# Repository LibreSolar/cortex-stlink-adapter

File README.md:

# Cortex ST-Link Adapter

This adapter allows to connect the ST-Link V2 (STM32 Nucleo boards) to be connected to the small 10-pin Cortex standard connectors.

The ST-Link can be used as a serial wire debug (SWD) interface.

## Schematic

The jumper JP1 can be used to connect the SWO pin (serial wire output) to the RX pin of the nucleo board, thus allowing serial communications with MCUs which don't have SWO (Cortex M0 like STM32F072 for example). This works only if the Cortex SWO pin is wired to a TX pin of the MCU, of course.

The pull-up resistor is useful to put NRST to a defined state.

The additional capacitor C1 can be used to stabilize the supply voltage, but might not be necessary.

## Original pictures

### Top side

### Bottom side (fits to ST-Link on Nucleo Board)

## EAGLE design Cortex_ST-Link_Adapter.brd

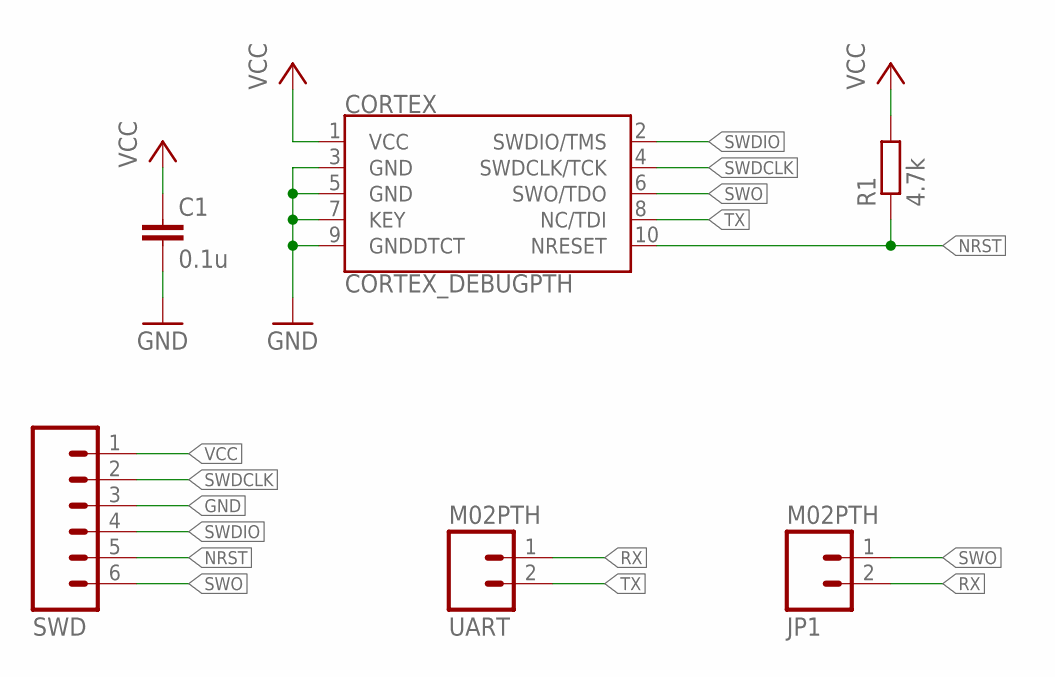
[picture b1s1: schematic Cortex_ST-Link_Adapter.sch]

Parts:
C1: 0.1u; C0805
CORTEX: CORTEX_DEBUGPTH; 2X5-PTH-1.27MM
JP1: M02PTH; 1X02
R1: 4.7k; R0805
SWD: M06SILK_FEMALE_PTH; 1X06
UART: M02PTH; 1X02

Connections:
GND: C1.2, CORTEX.3 (GND), CORTEX.5 (GND), CORTEX.7 (KEY), CORTEX.9 (GNDDTCT), SWD.3
NRST: CORTEX.10 (NRESET), R1.1, SWD.5
RX: JP1.2, UART.1
SWDCLK: CORTEX.4 (SWDCLK/TCK), SWD.2
SWDIO: CORTEX.2 (SWDIO/TMS), SWD.4
SWO: CORTEX.6 (SWO/TDO), JP1.1, SWD.6
TX: CORTEX.8 (NC/TDI), UART.2
VCC: C1.1, CORTEX.1 (VCC), R1.2, SWD.1

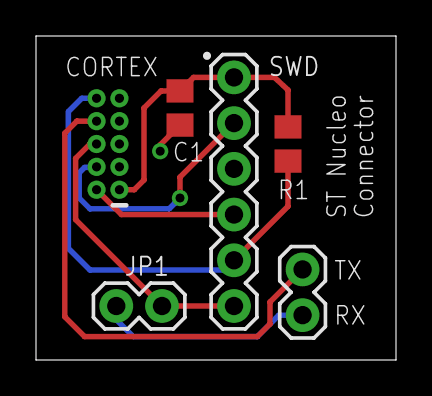
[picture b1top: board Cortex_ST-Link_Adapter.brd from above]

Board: 2 copper layers, 20.0 x 18.0 mm, 6 parts (0 on the bottom side), 8 nets.

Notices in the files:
parts and their libraries:
SparkFun-Connectors: Licensing: Creative Commons ShareAlike 4.0 International - https://creativecommons.org/licenses/by-sa/4.0
